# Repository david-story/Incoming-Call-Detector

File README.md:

# Incoming-Call-Detector
Based on circuit from http://www.circuitstoday.com/mobile-incoming-call-indicator
PCB created by David Story and David House for soldering workshop.

### PCB Image

### General
PCB created in Eagle for a small incoming call detector for your cellphone. This board was created to help teach students introductory soldering with through-hole components. There will be another repository shortly with a board for SMD soldering practice.

The circuit for this board works by having the board placed near your cell phone. While your phone is place on silent, the transmitter of the phone will still be activated, and will produce a frequency of around 900 MHz. The circuit will pick this up with its 10 uH coil, and the signal will be amplified, illuminating an LED to give you a visual indication that your phone is buzzing. <a href="http://www.circuitstoday.com/mobile-incoming-call-indicator">[1]</a>

### Dependencies
No dependencies, uses standard Eagle Library parts. Creating in Eagle Version 9.2.2 Education

### Installation 
1) Download files either from site or by using git clone https://github.com/david-story/IncomingCallDetector.git
2) Open a new Eagle Project
3) Drag and Drop the schematic and board files to your new project
4) You can now edit and/or create gerber files.

### Schematic

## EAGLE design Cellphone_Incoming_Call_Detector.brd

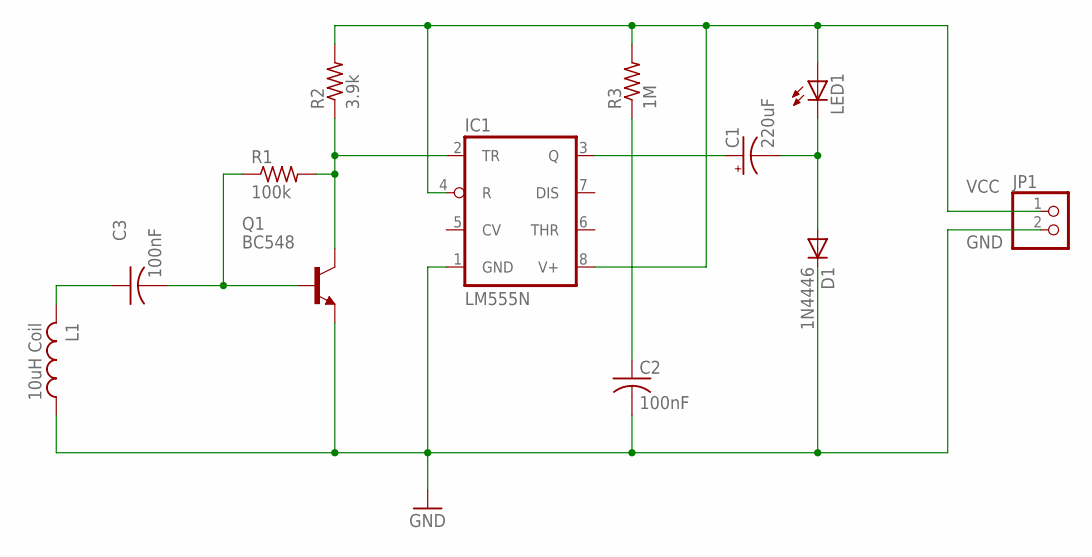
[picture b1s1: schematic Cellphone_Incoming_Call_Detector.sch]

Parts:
C1: 220uF; E3,5-8
C2, C3: 100nF; C025-025X050
D1: 1N4446; DO35-10
IC1: LM555N; DIL08
JP1: PINHD-1X2; 1X02
L1: 10uH Coil; 0204/7
LED1: LED5MM
Q1: BC548; TO92-EBC
R1: 100k; 0204/7
R2: 3.9k; 0204/7
R3: 1M; 0204/7

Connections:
GND: C2.2, D1.C, IC1.1 (GND), JP1.2, L1.1, Q1.E
unnamed: C1.+, IC1.3 (Q)
unnamed: C1.-, D1.A, LED1.K (C)
unnamed: C2.1, R3.1
unnamed: C3.2, Q1.B, R1.1
unnamed: IC1.2 (TR), Q1.C, R1.2, R2.1
unnamed: C3.1, L1.2
VCC: IC1.4 (R), IC1.8 (V+), JP1.1, LED1.A, R2.2, R3.2

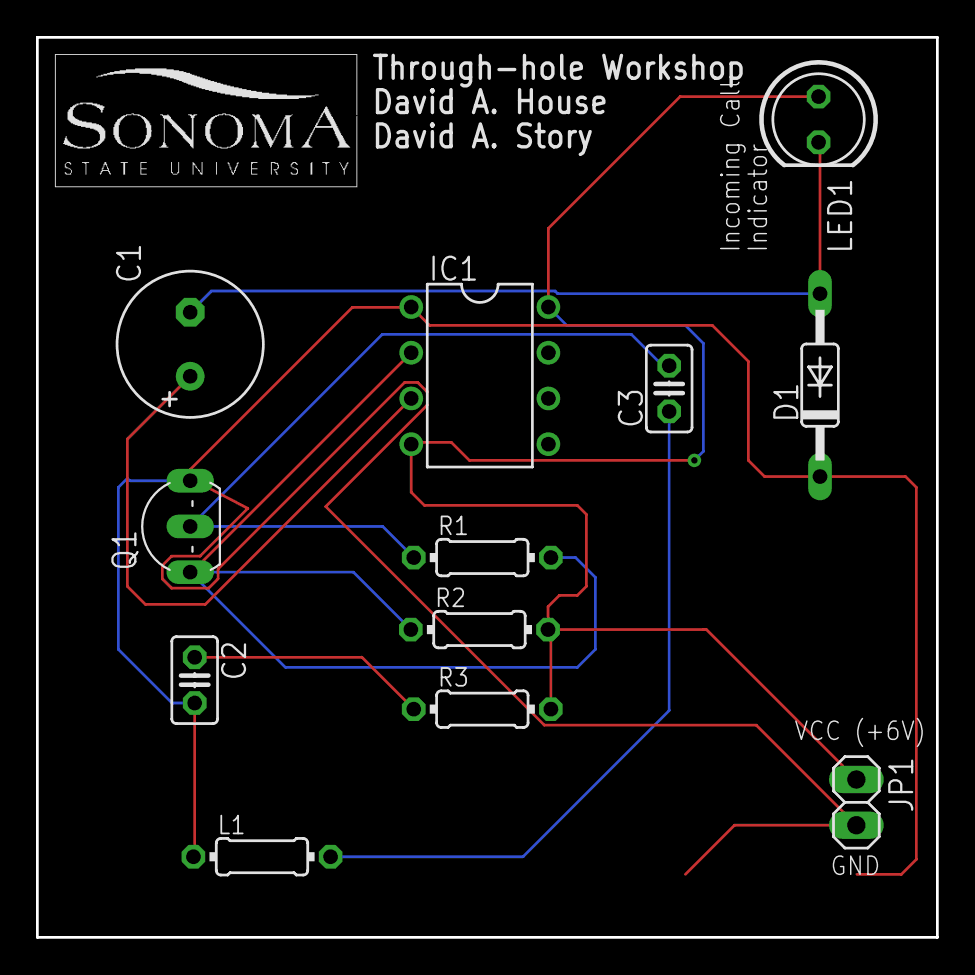
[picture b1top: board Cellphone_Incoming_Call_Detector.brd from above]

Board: 2 copper layers, 50.0 x 50.0 mm, 12 parts (0 on the bottom side), 8 nets.

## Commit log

2018-11-24 Eagle Files
    Board and Schematic Files
2018-11-24 Eagle Project File
    Eagle Project File
2018-11-24 Added images
2018-11-24 Update README.md
    added image
2018-11-24 Update .gitattributes
    added Eagle as repository "language"
2018-11-24 new images
    new images
